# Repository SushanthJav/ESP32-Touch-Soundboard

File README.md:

# ESP32-Touch-Soundboard
This ESP32 Project is a piece of embedded hardware that contains a touch screen, display and audio output. The main part of 

the device is the ESP32 microcontroller. The ESP32 communicates with the 2.8" ILI9341 SPI TFT display allowing visual output.

Inputs are provided by the physical buttons and touch screen. Audio is provided by the ESP32 reading audio files from the 

internal flash memory (using the littleFS file system) and sending the audio signal to the ESP32’s DAC. The signal is

amplified by the onboard PAM8302 Class-D mono amplifier to power the external 8 Ohm mini speaker. The traces have been routed 

carefully so that there are no issues with digital signal interference with the audio signals. This device has been created on 

a bespoke 71x71mm PCB created using JLCPCB.

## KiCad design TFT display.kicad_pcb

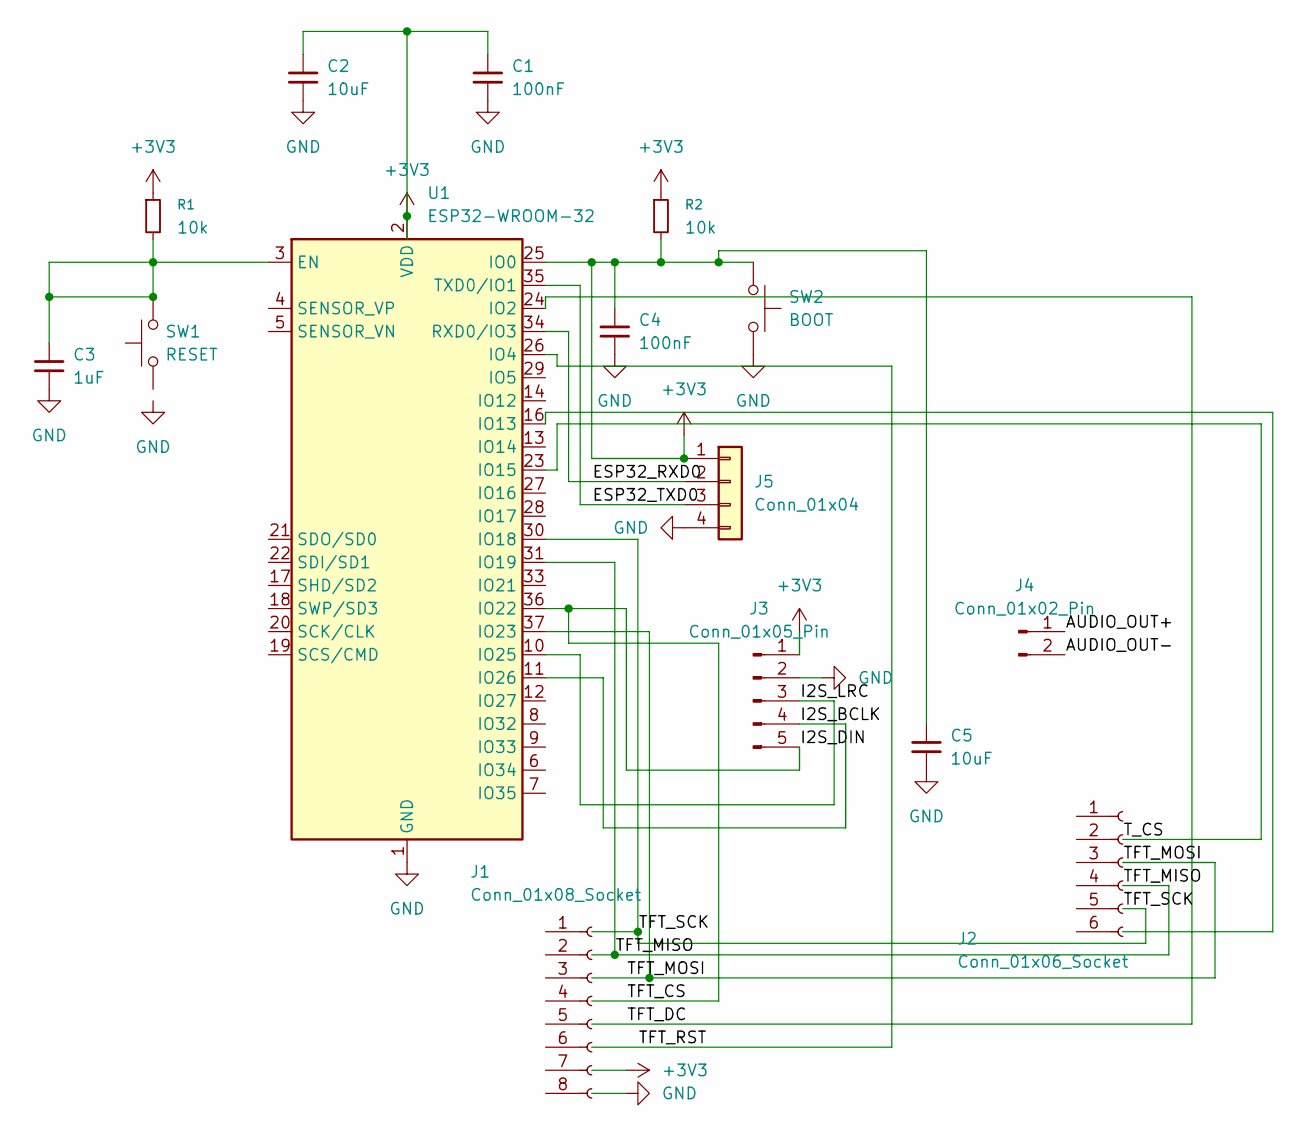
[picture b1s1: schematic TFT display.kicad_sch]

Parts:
C1, C4: 100nF; C_Disc_D3.0mm_W1.6mm_P2.50mm
C2, C5: 10uF; C_Radial_D5.0mm_H11.0mm_P2.00mm
C3: 1uF; C_Disc_D3.0mm_W1.6mm_P2.50mm
J1: Conn_01x08_Socket; PinSocket_1x08_P2.54mm_Vertical
J2: Conn_01x06_Socket; PinSocket_1x06_P2.54mm_Vertical
J3: Conn_01x05_Pin; PinHeader_1x05_P2.54mm_Vertical
J4: Conn_01x02_Pin; PinHeader_1x02_P2.54mm_Vertical
J5: Conn_01x04; PinHeader_1x04_P2.54mm_Vertical
R1, R2: 10k; R_Axial_DIN0204_L3.6mm_D1.6mm_P7.62mm_Horizontal
SW1: RESET; SW_PUSH_6mm
SW2: BOOT; SW_PUSH_6mm
U1: ESP32-WROOM-32

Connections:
+3V3: C1.1, C2.1, C4.1, C5.1, J3.1, J5.1, R1.1, R2.1, R2.2, SW2.1, U1.2 (VDD), U1.25 (IO0)
/AUDIO_OUT+: J4.1
/AUDIO_OUT-: J4.2
/ESP32_RXD0: J5.2, U1.34 (RXD0/IO3)
/ESP32_TXD0: J5.3, U1.35 (TXD0/IO1)
/I2S_BCLK: J3.4, U1.11 (IO26)
/I2S_DIN: J3.5, U1.36 (IO22)
/I2S_LRC: J3.3, U1.10 (IO25)
/TFT_DC: U1.24 (IO2)
/TFT_MISO: U1.31 (IO19)
/TFT_MOSI: U1.37 (IO23)
/TFT_RST: U1.26 (IO4)
/TFT_SCK: U1.30 (IO18)
/T_CS: U1.23 (IO15)
GND: C1.2, C2.2, C3.2, C4.2, C5.2, J3.2, J5.4, SW2.2, U1.1 (GND), U1.15 (GND), U1.38 (GND), U1.39 (GND)
unnamed: C3.1, R1.2, SW1.2 (2_2), U1.3 (EN)

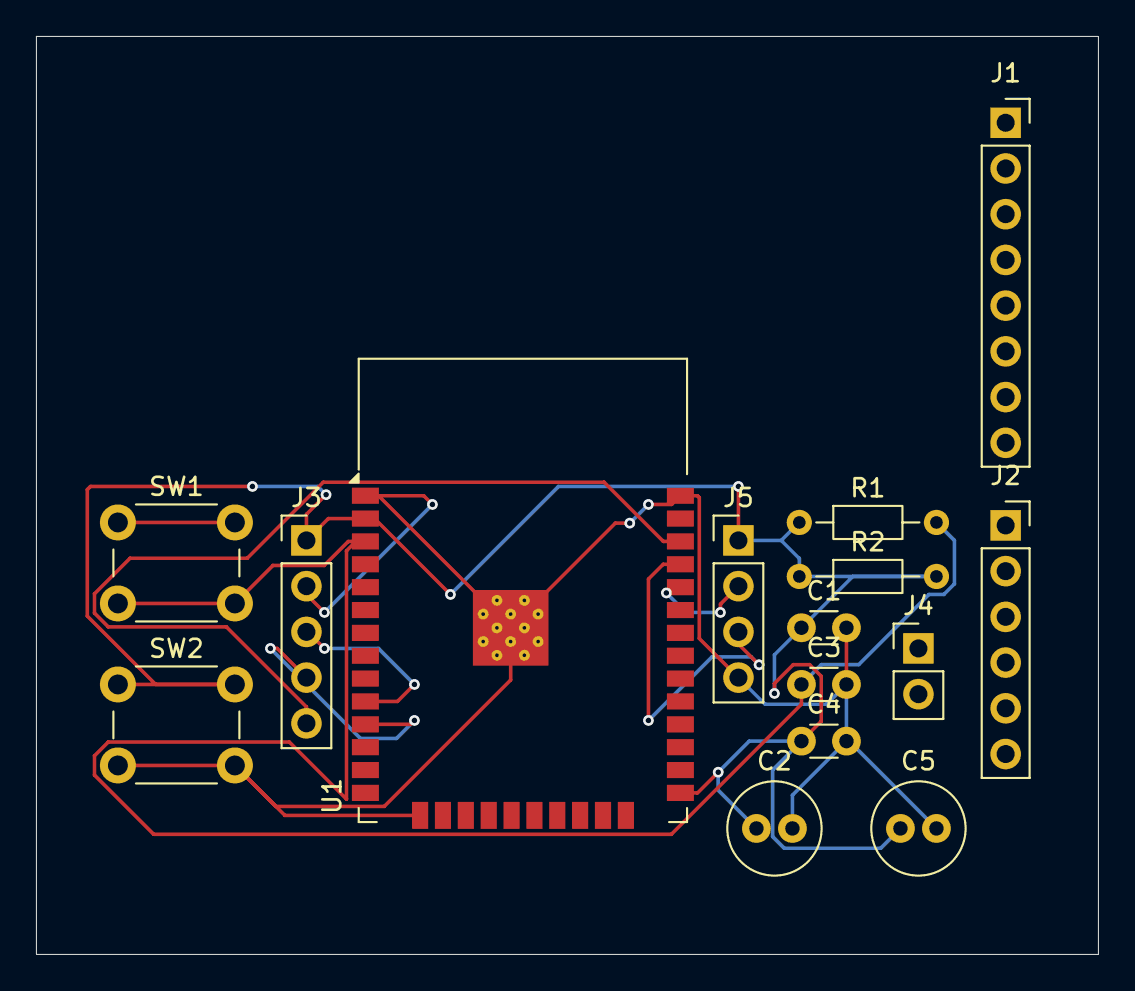
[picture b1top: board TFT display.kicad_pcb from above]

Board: 2 copper layers, 59.0 x 51.0 mm, 15 parts (0 on the bottom side), 8 nets.
